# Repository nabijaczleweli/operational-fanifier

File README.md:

# operational-fanifier 
This blows!

## What?

Automatic analogue tunable temperature-activated fan for the inside of one of my ATX supplies.

## Why?

The original fan is (a) loud and (b) runs continuously, this will probably help avoid the first through cutting down on the second.

## Whom with?

An [LM324N Op-Amp](//ti.com/lit/ds/symlink/lm324-n.pdf),
a [74HC32 Quad OR Gate](//mouser.com/ds/2/308/74HC32.REV1-102593.pdf),
a [LM335Z Kelvin-Calibrated Temperature Sensor](//ti.com/lit/ds/symlink/lm335.pdf),
and a handful of generics.

## How?

#### Schematic

#### Short description

Starting from the top-left, we can see the Temperature Sensor (`U3`), to be mounted onto the target heatsink, leading into an op-amp unit (`U1D`),
  which compares it to the customisable potentiometer (`RV1`) voltage divider.
As for the use of a quad op-amp when using only one unit thereof – these were vastly (15x/pc.) cheaper at my local shop,
  and have not been chosen due to any specific characteristics.

Thus, if the reading from the Sensor is higher than the pre-set voltage, the output will also go high, which will lead to two things:
  (a) pulling one input of the primary OR gate (`U2A`) high, and
  (b) charging the timing capacitor (`C3`) via the timing input transistor (`Q1`).

The timing capacitor's discharge rate can be controlled via the customisable potentiometer (`RV2`),
  which will, with the given `C1 = 33µF`, `R3 = 100kΩ`, and `RV2 = 1MΩ` values and the datasheet-specified threshold voltage of `Vₜₕ = 0.7V𝒸𝒸`
  as well as perfect linearity and full opening charge, vary between `(1 - 0.7) * 33µF * (100kΩ + 0) = 0.99s` and `(1 - 0.7) * 33µF * (100kΩ + 1MΩ) = 10.89s`.

The positive terminal of the timing capacitor is tied to the other input of the primary OR gate, meaning it will keep it active for longer than just the Sensor would.

The output fo the primary OR gate leads into one of the inputs of the secondary OR gate (`U2B`),
  whose second input is tied directly to a pulled-down bistable override switch (`SW1`),
  flipping whichof will turn on the fan (`M1`) regardless of any earlier autonomous stages (i.e. everything from the Sensor to the primary OR gate output).

Which means, that if either the override switch is on. the temperature sensor reads above the preuser-specified temperature,
  or the timer capacitor hasn't gone below the threshold voltage, the fan will be turned on via the primary transistor (`Q2`).

#### Layout

The layout is very cramped due to my use of a very peculiar perfboard; it probably could've been solved much cleaner otherwise.

#### Model

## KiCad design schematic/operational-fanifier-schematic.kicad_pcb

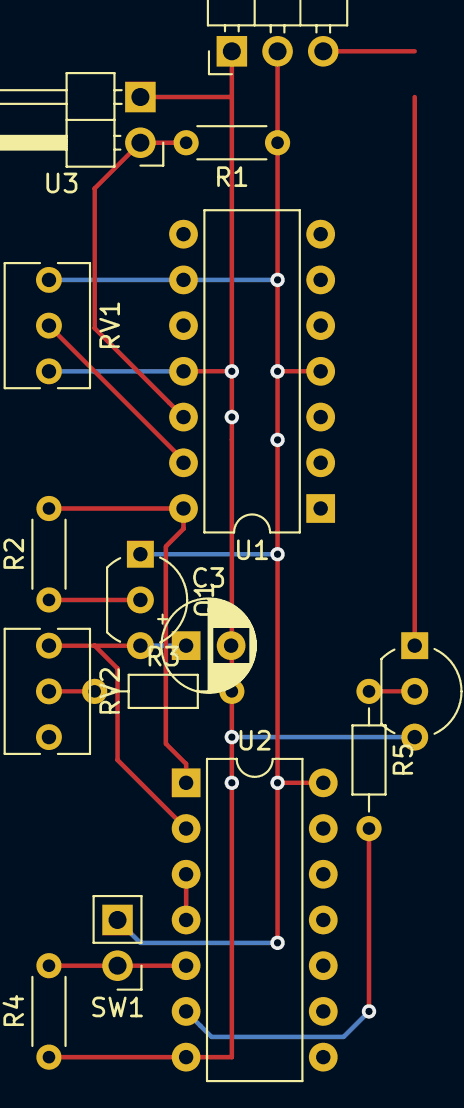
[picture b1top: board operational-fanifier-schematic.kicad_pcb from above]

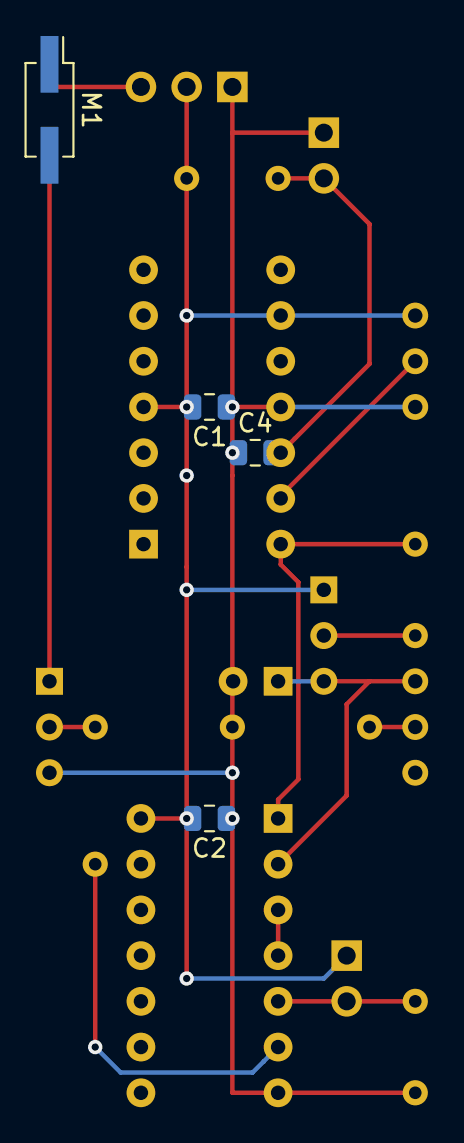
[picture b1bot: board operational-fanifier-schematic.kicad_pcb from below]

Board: 2 copper layers, 19 parts (4 on the bottom side), 14 nets.

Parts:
C1, C2: 100nF; C_0805_2012Metric
C3: 33µF; CP_Radial_D5.0mm_P2.50mm
C4: 10nF; C_0805_2012Metric
J1: Conn_01x03; PinHeader_1x03_P2.54mm_Horizontal
M1: Fan; PinHeader_2x01_P2.54mm_Vertical_SMD
Q1, Q2: BC337; TO-92_Inline_Wide
R1: 1k; R_Axial_DIN0204_L3.6mm_D1.6mm_P5.08mm_Horizontal
R2, R4: 2k2; R_Axial_DIN0204_L3.6mm_D1.6mm_P5.08mm_Horizontal
R3: 100k; R_Axial_DIN0204_L3.6mm_D1.6mm_P7.62mm_Horizontal
R5: 2k2; R_Axial_DIN0204_L3.6mm_D1.6mm_P7.62mm_Horizontal
RV1: 5kR_POT; Potentiometer_Bourns_3266Y_Vertical
RV2: 1MR_POT; Potentiometer_Bourns_3266Y_Vertical
SW1: SW_SPDT; PinHeader_1x02_P2.54mm_Vertical
U1: LM324N; DIP-14_W7.62mm
U2: 74HC32; DIP-14_W7.62mm
U3: LM335Z; PinHeader_1x02_P2.54mm_Horizontal

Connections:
+5V: C1.2, C2.2, J1.2, Q1.1, R1.1, RV1.3, U1.4, U1.9, U2.14
+12V: J1.3, M1.1
GND: C1.1, C2.1, C3.2, C4.1, J1.1, Q2.3, R3.2, R4.1, RV1.1, U1.11, U2.7, U3.1
unnamed: C3.1, Q1.3, RV2.3, U2.2
unnamed: C4.2, R1.2, U1.12, U3.2
unnamed: M1.2, Q2.1
unnamed: Q1.2, R2.1
unnamed: Q2.2, R5.1
unnamed: R2.2, U1.14, U2.1
unnamed: R3.1, RV2.2
unnamed: R4.2, SW1.2, U2.5
unnamed: R5.2, U2.6
unnamed: RV1.2, U1.13
unnamed: U2.3, U2.4

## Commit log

2019-02-24 Mostly-final layouted schematic
2019-02-24 Add layouted board
2019-02-24 Title b l o c c
2019-02-24 Add picture exports
    The render is absolutely *beautiul* though, like, holy shit
2019-02-24 Include KiCad exports in README. Add plaintext explanation to README
2019-03-01 Move the transistor to below the fan. Add test results with transistored
2019-03-01 Update the images too, whoops
2019-03-02 The threshold goes from the other way you big ole dumb-dumb
2019-04-15 Use two-pin footprints where applicable. Use horizontal headers for M1 and U3
2019-04-15 Don't flip when not required
2019-04-15 Bump version to 0.1.1 in exports
2019-04-15 I figured it out, thanks
2019-04-19 I really should think these things through
2019-04-19 Bump version to 0.1.2

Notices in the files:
README.md:
License: MIT
